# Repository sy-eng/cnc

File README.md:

# CNC

These are setting file for machinekit for CNC3060 with original board.

The CNC has 3D printer module.
The arduino file is for it.

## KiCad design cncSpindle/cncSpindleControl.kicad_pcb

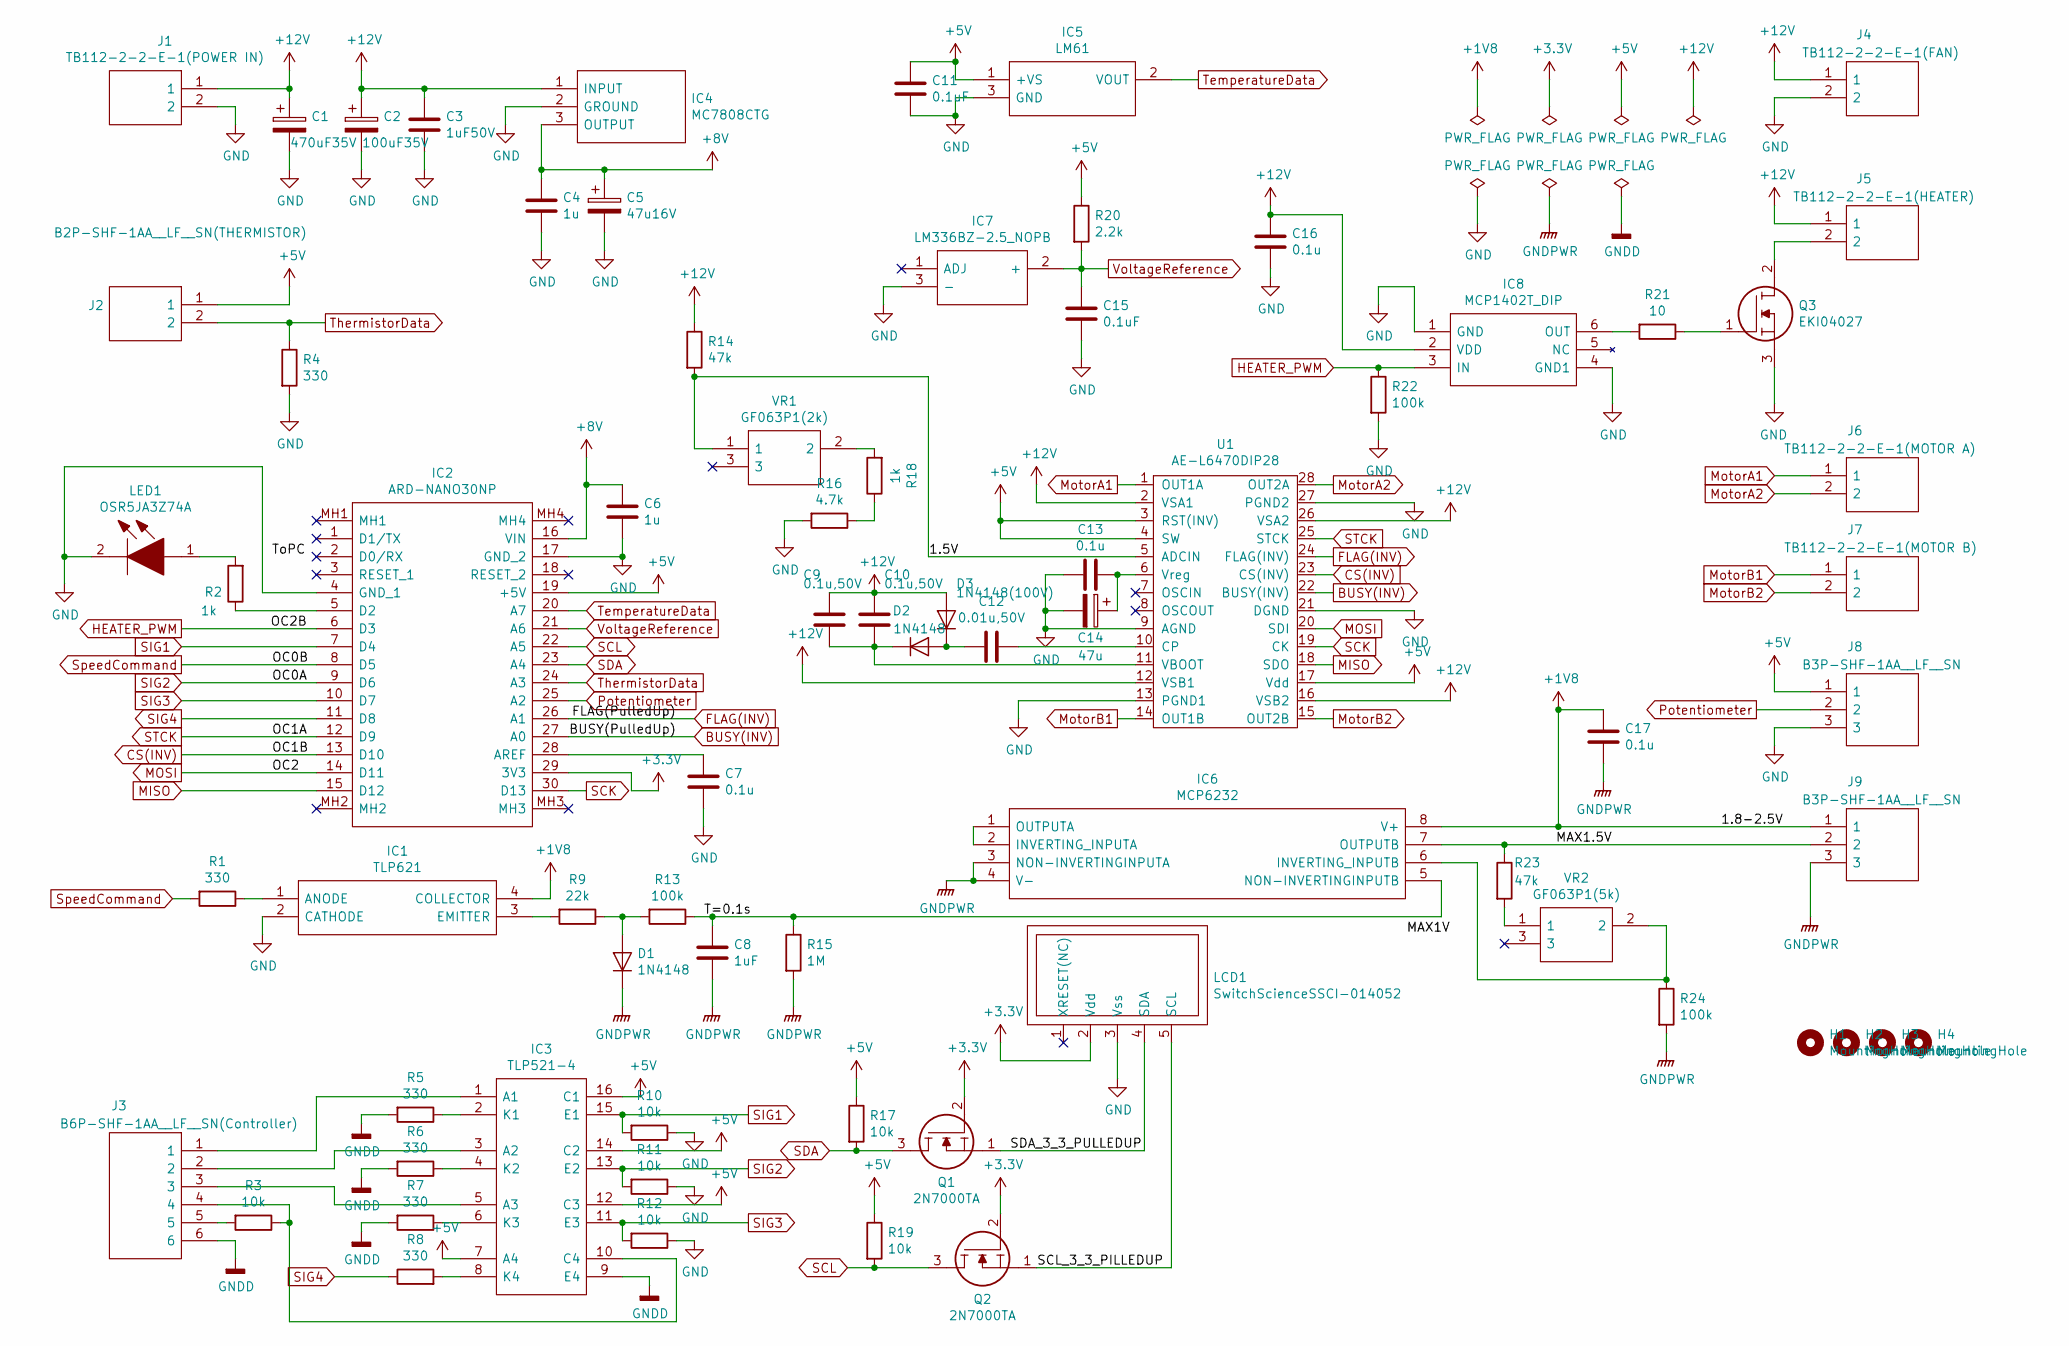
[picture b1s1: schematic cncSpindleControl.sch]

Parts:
C1: 470uF35V; CP_Radial_D10.0mm_P5.00mm
C2: 100uF35V; CP_Radial_D6.3mm_P2.50mm
C3: 1uF50V; C_Rect_L7.0mm_W2.0mm_P5.00mm
C4, C6: 1u; C_Rect_L7.0mm_W2.0mm_P5.00mm
C5: 47u16V; CP_Radial_D6.3mm_P2.50mm
C7: 0.1u; C_Rect_L9.0mm_W2.5mm_P7.50mm_MKT
C8: 1uF; C_Rect_L7.0mm_W2.0mm_P5.00mm
C9, C10: 0.1u,50V; C_Rect_L7.0mm_W2.0mm_P5.00mm
C11: 0.1uF; C_Rect_L7.0mm_W2.0mm_P5.00mm
C12: 0.01u,50V; C_Rect_L7.0mm_W2.0mm_P5.00mm
C13, C16, C17: 0.1u; C_Rect_L7.0mm_W2.0mm_P5.00mm
C14: 47u; CP_Radial_D6.3mm_P2.50mm
C15: 0.1uF; C_Rect_L9.0mm_W2.5mm_P7.50mm_MKT
D1, D2: 1N4148; D_T-1_P5.08mm_Horizontal
D3: 1N4148(100V); D_T-1_P5.08mm_Horizontal
H1, H2, H3, H4: MountingHole; MountingHole_3.2mm_M3_Pad
IC1: TLP621; DIP762W60P254L458H485Q4N; Manufacturer_Part_Number TLP621; Mouser Part Number 757-TLP621
IC2: ARD-NANO30NP; ARDNANO30NP; Manufacturer_Part_Number ARD-NANO30NP; Mouser Part Number 992-ARD-NANO30NP
IC3: TLP521-4; DIP762W60P254L1982H400Q16N; Manufacturer_Part_Number TLP521-4
IC4: MC7808CTG; TO254P482X997X2018-3P; Manufacturer_Part_Number MC7808CTG; Mouser Part Number 863-MC7808CTG
IC5: LM61; LP0003A; Manufacturer_Part_Number LM35DZ/NOPB; Mouser Part Number 926-LM35DZ/NOPB
IC6: MCP6232; CDIP775W53P254L1016H508Q8; Manufacturer_Part_Number LMC6482AMJ/883; Mouser Part Number 595-LMC6482AMJ/883
IC7: LM336BZ-2.5_NOPB; LM336BZ25NOPB; Manufacturer_Part_Number LM336BZ-2.5/NOPB; Mouser Part Number 926-LM336BZ-2.5/NOPB
IC8: MCP1402T_DIP; AKIDUKI_SOT23_DIP-6_W7.62mm; Manufacturer_Part_Number MCP1402T-E/OT; Mouser Part Number 579-MCP1402T-E/OT
J1: TB112-2-2-E-1(POWER IN); TB11222E1; Manufacturer_Part_Number TB112-2-2-E-1
J2: B2P-SHF-1AA__LF__SN(THERMISTOR); HDRV2W64P0X250_1X2_500X560X920P; Manufacturer_Part_Number BS2P-SHF-1AA (LF)(SN)
J3: B6P-SHF-1AA__LF__SN(Controller); HDRV6W64P0X250_1X6_1500X560X920P; Manufacturer_Part_Number BS6P-SHF-1AA (LF)(SN)
J4: TB112-2-2-E-1(FAN); TB11222E1; Manufacturer_Part_Number TB112-2-2-E-1
J5: TB112-2-2-E-1(HEATER); TB11222E1; Manufacturer_Part_Number TB112-2-2-E-1
J6: TB112-2-2-E-1(MOTOR A); TB11222E1; Manufacturer_Part_Number TB112-2-2-E-1
J7: TB112-2-2-E-1(MOTOR B); TB11222E1; Manufacturer_Part_Number TB112-2-2-E-1
J8, J9: B3P-SHF-1AA__LF__SN; HDRV3W80P0X250_1X3_750X560X920P; Manufacturer_Part_Number BS3P-SHF-1AA (LF)(SN)
LCD1: SwitchScienceSSCI-014052; SwitchScienceSSCI-014076
LED1: OSR5JA3Z74A; Manufacturer_Part_Number OSR5JA3Z74A
Q1, Q2: 2N7000TA; TO-92_3L_(AMMO); Manufacturer_Part_Number 2N7000TA; Mouser Part Number 512-2N7000TA
Q3: EKI04027; TO254P470X990X1965-3P; Manufacturer_Part_Number EKI04027
R1, R4, R8: 330; R_Axial_DIN0207_L6.3mm_D2.5mm_P7.62mm_Horizontal
R2, R18: 1k; R_Axial_DIN0207_L6.3mm_D2.5mm_P7.62mm_Horizontal
R3: 10k; R_0603_1608Metric_Pad1.05x0.95mm_HandSolder
R5, R6, R7: 330; R_0603_1608Metric_Pad1.05x0.95mm_HandSolder
R9: 22k; R_Axial_DIN0207_L6.3mm_D2.5mm_P7.62mm_Horizontal
R10, R11, R12, R17, R19: 10k; R_Axial_DIN0207_L6.3mm_D2.5mm_P7.62mm_Horizontal
R13, R22, R24: 100k; R_Axial_DIN0207_L6.3mm_D2.5mm_P7.62mm_Horizontal
R14, R23: 47k; R_Axial_DIN0207_L6.3mm_D2.5mm_P7.62mm_Horizontal
R15: 1M; R_Axial_DIN0207_L6.3mm_D2.5mm_P7.62mm_Horizontal
R16: 4.7k; R_Axial_DIN0207_L6.3mm_D2.5mm_P7.62mm_Horizontal
R20: 2.2k; R_Axial_DIN0207_L6.3mm_D2.5mm_P7.62mm_Horizontal
R21: 10; R_Axial_DIN0207_L6.3mm_D2.5mm_P7.62mm_Horizontal
U1: AE-L6470DIP28
VR1: GF063P1(2k); GF063P1; Manufacturer_Part_Number GF063P1
VR2: GF063P1(5k); GF063P1; Manufacturer_Part_Number GF063P1

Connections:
+1V8: C17.1, IC1.4 (COLLECTOR), IC6.8 (V+), J9.1
+3V3: IC2.29 (3V3), LCD1.2 (Vdd), Q1.2, Q2.2
+5V: C11.1, IC2.19 (+5V), IC3.7 (A4), IC3.12 (C3), IC3.14 (C2), IC3.16 (C1), IC5.1 (+VS), J2.1, J8.1, R17.1, R19.1, R20.1, U1.3 (RST(INV)), U1.4 (SW), U1.17 (Vdd)
+8V: C4.1, C5.1, C6.1, IC2.16 (VIN), IC4.3 (OUTPUT)
+12V: C1.1, C2.1, C3.1, C9.1, C10.1, C16.1, D3.2 (A), IC4.1 (INPUT), IC8.2 (VDD), J1.1, J4.1, J5.1, R14.1, U1.2 (VSA1), U1.12 (VSB1), U1.16 (VSB2), U1.26 (VSA2)
/1.5V: R14.2, U1.5 (ADCIN), VR1.1
/MAX1.5V: IC6.7 (OUTPUTB), J9.2, R23.1
/SCL_3_3_PILLEDUP: LCD1.5 (SCL), Q2.1
/SDA_3_3_PULLEDUP: LCD1.4 (SDA), Q1.1
/T=0.1s: C8.1, IC6.5 (NON-INVERTINGINPUTB), R13.1, R15.1
BUSY(INV): IC2.27 (A0), U1.22 (BUSY(INV))
CS(INV): IC2.13 (D10), U1.23 (CS(INV))
FLAG(INV): IC2.26 (A1), U1.24 (FLAG(INV))
GND: C1.2, C2.2, C3.2, C4.2, C5.2, C6.2, C7.2, C11.2, C13.2, C14.2, C15.2, C16.2, IC1.2 (CATHODE), IC2.4 (GND_1), IC2.17 (GND_2), IC4.2 (GROUND), IC5.3 (GND), IC7.3 (-), IC8.1 (GND), IC8.4 (GND1), J1.2, J4.2, J8.3, LCD1.3 (Vss), LED1.2, Q3.3, R4.2, R10.1, R11.1, R12.1, R16.2, R22.2, U1.9 (AGND), U1.13 (PGND1), U1.21 (DGND), U1.27 (PGND2)
GNDD: IC3.9 (E4), J3.6, R5.2, R6.2, R7.2
GNDPWR: C8.2, C17.2, D1.1 (K), IC6.3 (NON-INVERTINGINPUTA), IC6.4 (V-), J9.3, R15.2, R24.2
HEATER_PWM: IC2.6 (D3), IC8.3 (IN), R22.1
MISO: IC2.15 (D12), U1.18 (SDO)
MOSI: IC2.14 (D11), U1.20 (SDI)
MotorA1: J6.1, U1.1 (OUT1A)
MotorA2: J6.2, U1.28 (OUT2A)
MotorB1: J7.1, U1.14 (OUT1B)
MotorB2: J7.2, U1.15 (OUT2B)
unnamed: C7.1, IC2.28 (AREF)
unnamed: C9.2, C10.2, D2.1 (K), U1.11 (VBOOT)
unnamed: C12.1, U1.10 (CP)
unnamed: C12.2, D2.2 (A), D3.1 (K)
unnamed: C13.1, C14.1, U1.6 (Vreg)
unnamed: D1.2 (A), R9.1, R13.2
unnamed: IC1.1 (ANODE), R1.1
unnamed: IC1.3 (EMITTER), R9.2
unnamed: IC2.5 (D2), R2.1
unnamed: IC3.1 (A1), J3.1
unnamed: IC3.2 (K1), R5.1
unnamed: IC3.3 (A2), J3.2
unnamed: IC3.4 (K2), R6.1
unnamed: IC3.5 (A3), J3.3
unnamed: IC3.6 (K3), R7.1
unnamed: IC3.8 (K4), R8.2
unnamed: IC3.10 (C4), J3.4, R3.1
unnamed: IC6.1 (OUTPUTA), IC6.2 (INVERTING_INPUTA)
unnamed: IC6.6 (INVERTING_INPUTB), R24.1, VR2.2
unnamed: IC8.6 (OUT), R21.2
unnamed: J3.5, R3.2
unnamed: J5.2, Q3.2
unnamed: LED1.1, R2.2
unnamed: Q3.1, R21.1
unnamed: R16.1, R18.1
unnamed: R18.2, VR1.2
unnamed: R23.2, VR2.1
Potentiometer: IC2.25 (A2), J8.2
SCK: IC2.30 (D13), U1.19 (CK)
SCL: IC2.22 (A5), Q2.3, R19.2
SDA: IC2.23 (A4), Q1.3, R17.2
SIG1: IC2.7 (D4), IC3.15 (E1), R10.2
SIG2: IC2.9 (D6), IC3.13 (E2), R11.2
SIG3: IC2.10 (D7), IC3.11 (E3), R12.2
SIG4: IC2.11 (D8), R8.1
STCK: IC2.12 (D9), U1.25 (STCK)
SpeedCommand: IC2.8 (D5), R1.2
TemperatureData: IC2.20 (A7), IC5.2 (VOUT)
ThermistorData: IC2.24 (A3), J2.2, R4.1
VoltageReference: C15.1, IC2.21 (A6), IC7.2 (+), R20.2

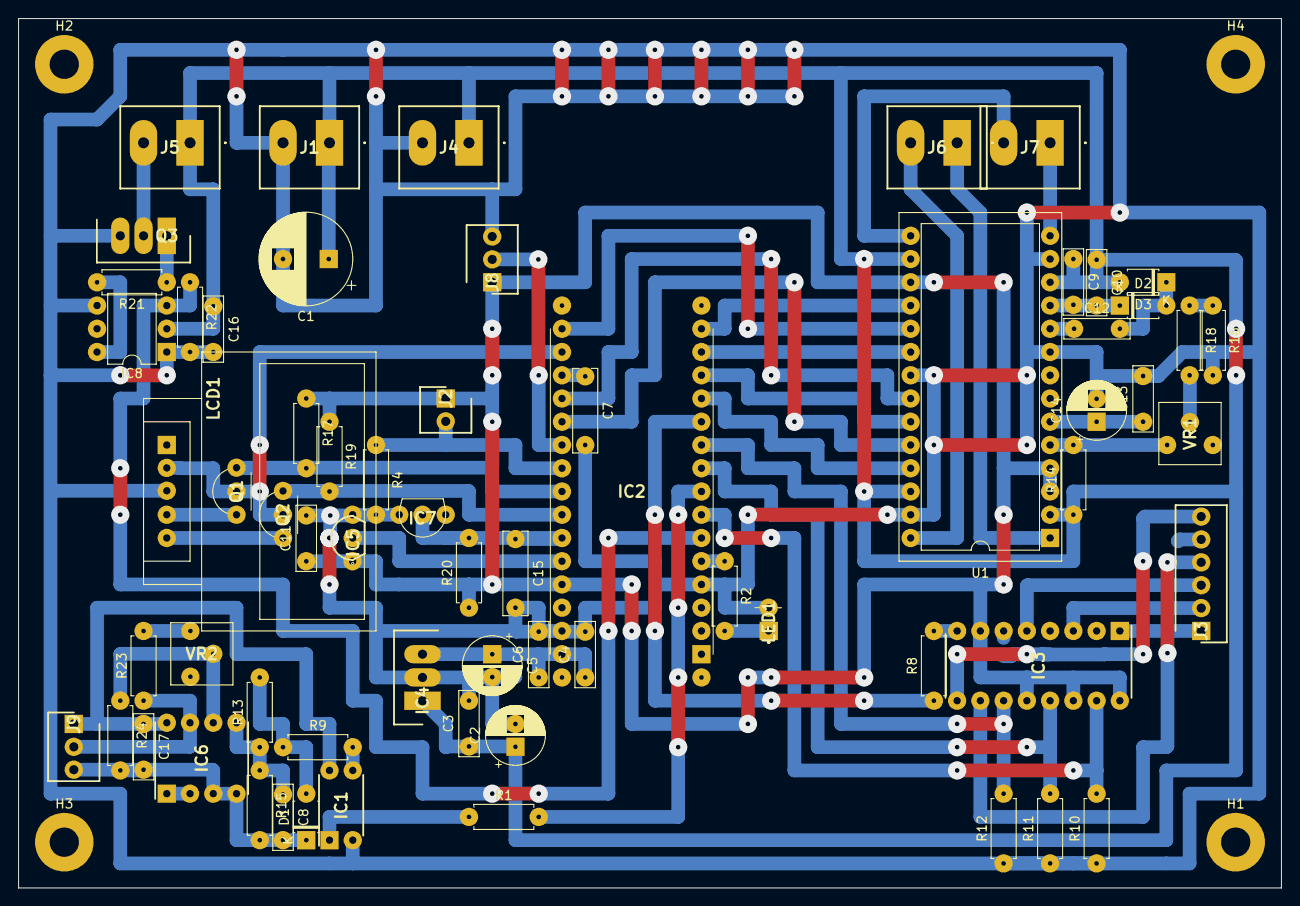
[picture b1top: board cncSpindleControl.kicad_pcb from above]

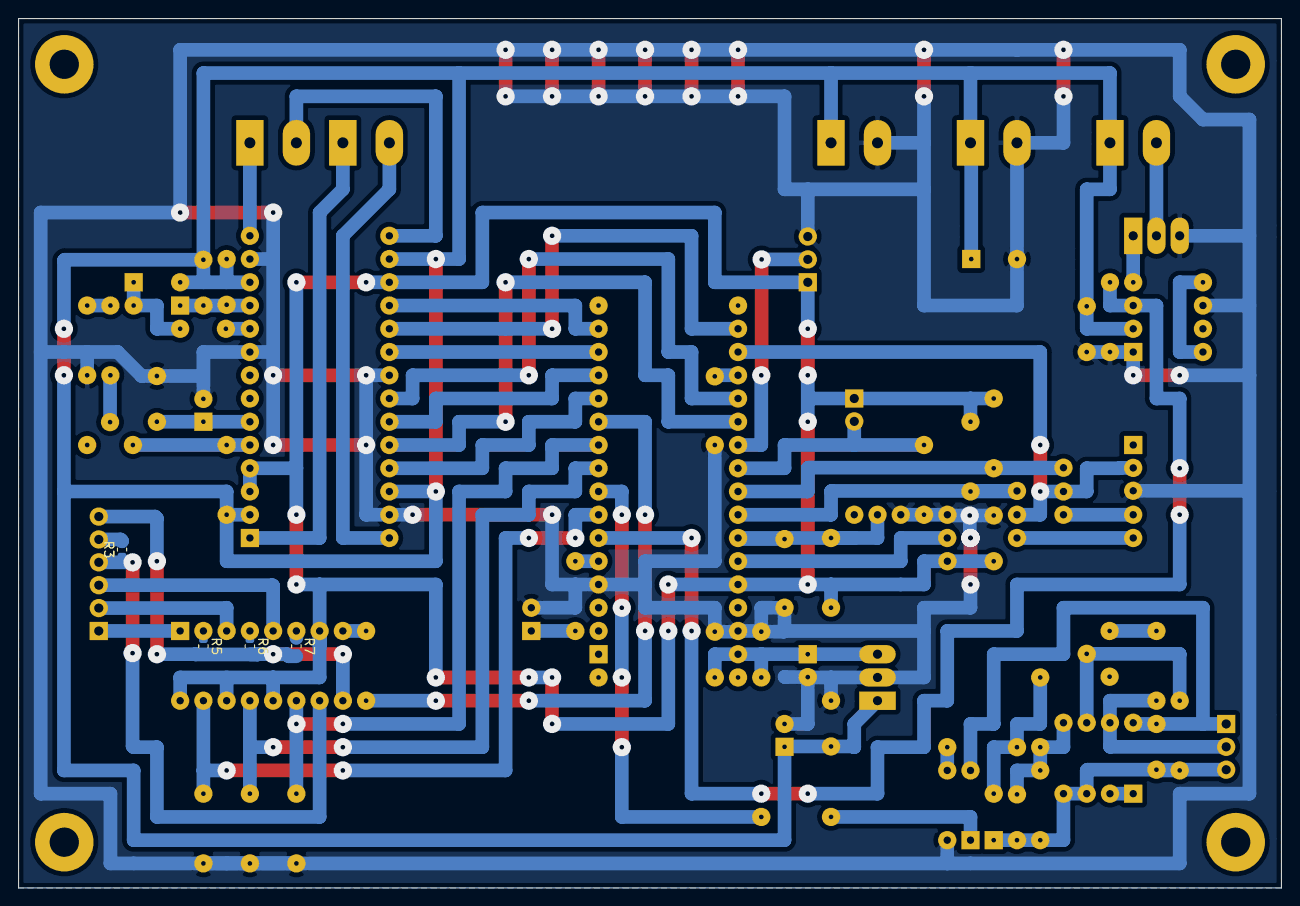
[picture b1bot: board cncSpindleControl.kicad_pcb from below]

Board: 2 copper layers, 138.0 x 95.0 mm, 73 parts (4 on the bottom side), 63 nets.

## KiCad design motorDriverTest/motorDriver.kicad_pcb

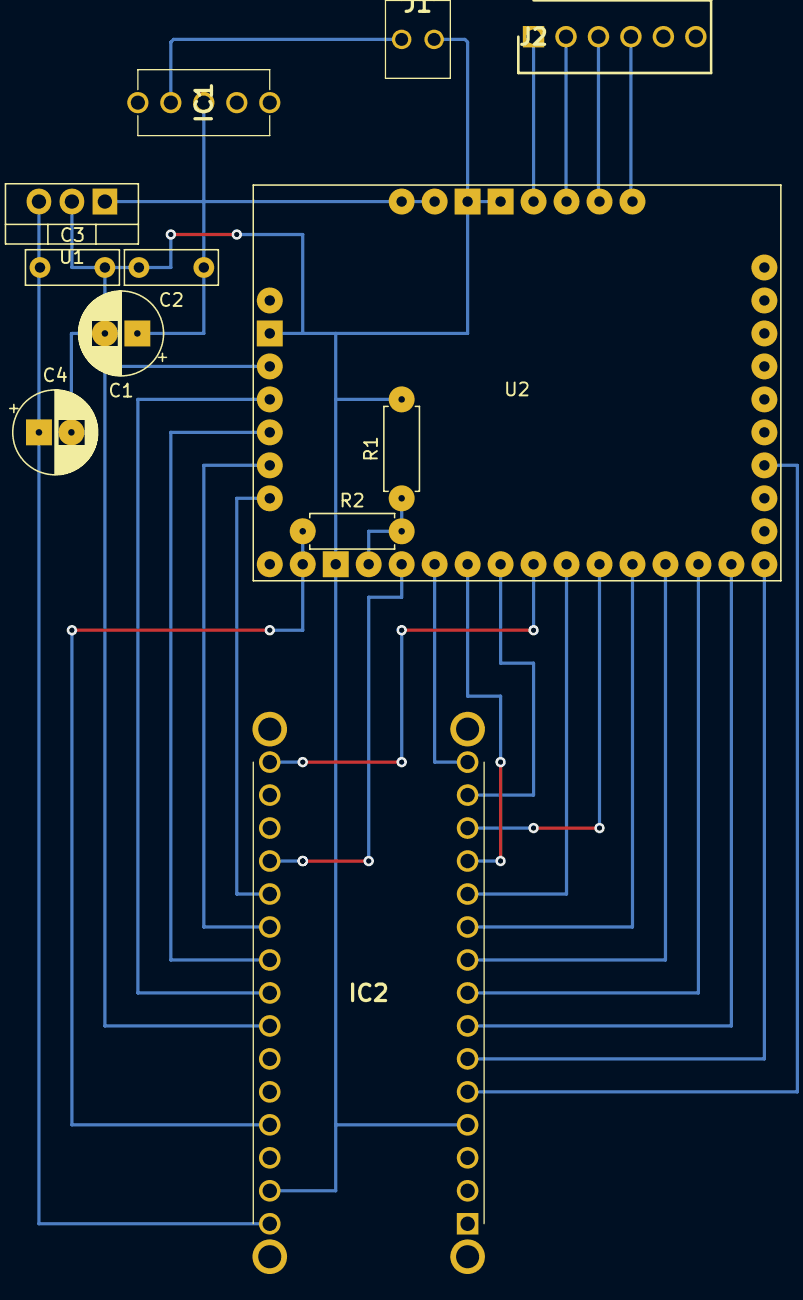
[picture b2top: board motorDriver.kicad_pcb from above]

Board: 2 copper layers, 12 parts (0 on the bottom side), 28 nets.

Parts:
C1, C4: 47u; CP_Radial_D6.3mm_P2.50mm
C2, C3: 0.1u; C_Rect_L7.0mm_W2.5mm_P5.00mm
IC1: 2MS1T1B4VS2QES
IC2: ARD-NANO30NP; ARDNANO30NP
J1: BS2P-SHF-1AA__LF__SN_; BS2PSHF1AALFSN
J2: B6P-SHF-1AA__LF__SN_; HDRV6W64P0X250_1X6_1250X560X920P
R1: 33k; R_Axial_DIN0207_L6.3mm_D2.5mm_P7.62mm_Horizontal
R2: 22k; R_Axial_DIN0207_L6.3mm_D2.5mm_P7.62mm_Horizontal
U1: LM7807_TO220; TO-220-3_Vertical
U2: POLOLU_TB67S128FTG_BOARD

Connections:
+5V: IC2.19, R2.1, U2.4
+8V: C3.1, C4.1, IC2.16, U1.3
+12V: C1.1, C2.1, IC1.2, U1.1, U2.33, U2.34
GND: C1.2, C2.2, C3.2, C4.2, IC2.4, IC2.17, J1.1, R1.2, U1.2, U2.2, U2.5, U2.35, U2.36
unnamed: IC1.1, J1.2
unnamed: IC2.5, U2.21
unnamed: IC2.6, U2.18
unnamed: IC2.7, U2.17
unnamed: IC2.8, U2.16
unnamed: IC2.9, U2.15
unnamed: IC2.10, U2.14
unnamed: IC2.11, U2.12
unnamed: IC2.12, U2.9
unnamed: IC2.13, U2.13
unnamed: IC2.14, U2.10
unnamed: IC2.15, U2.8
unnamed: IC2.22, U2.28
unnamed: IC2.23, U2.29
unnamed: IC2.24, U2.30
unnamed: IC2.25, U2.31
unnamed: IC2.26, U2.32
unnamed: IC2.27, U2.7
unnamed: IC2.30, U2.11
unnamed: J2.1, U2.37
unnamed: J2.2, U2.38
unnamed: J2.3, U2.39
unnamed: J2.4, U2.40
unnamed: R1.1, R2.2, U2.6

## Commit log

2020-06-15 add CNC3060 setting files and arduino file for 3D printer unit
2020-06-15 modified README.md
2020-08-23 This program control the 3D printer unit.
2020-08-23 This program controls the 3D printer unit.
2021-06-12 Rename README.md to cncSpindle/README.md
2021-06-12 Rename cncSpindle/README.md to README.md
2021-12-29 Rename 3DprinterSensor.ino to motorDriverTest/3DprinterSensor.ino
2021-12-29 Rename motorDriverTest/3DprinterSensor.ino to 3DprinterSensor.ino
